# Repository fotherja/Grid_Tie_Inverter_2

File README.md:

# Grid_Tie_Inverter_2
Version 2 of the GTI project

Here are the Eagle files for the grid tie inverter H-Bridge and voltage sense board.

And all the software that runs on and STM32f407 dev board.

Please see a full description of the project on instrucatbles

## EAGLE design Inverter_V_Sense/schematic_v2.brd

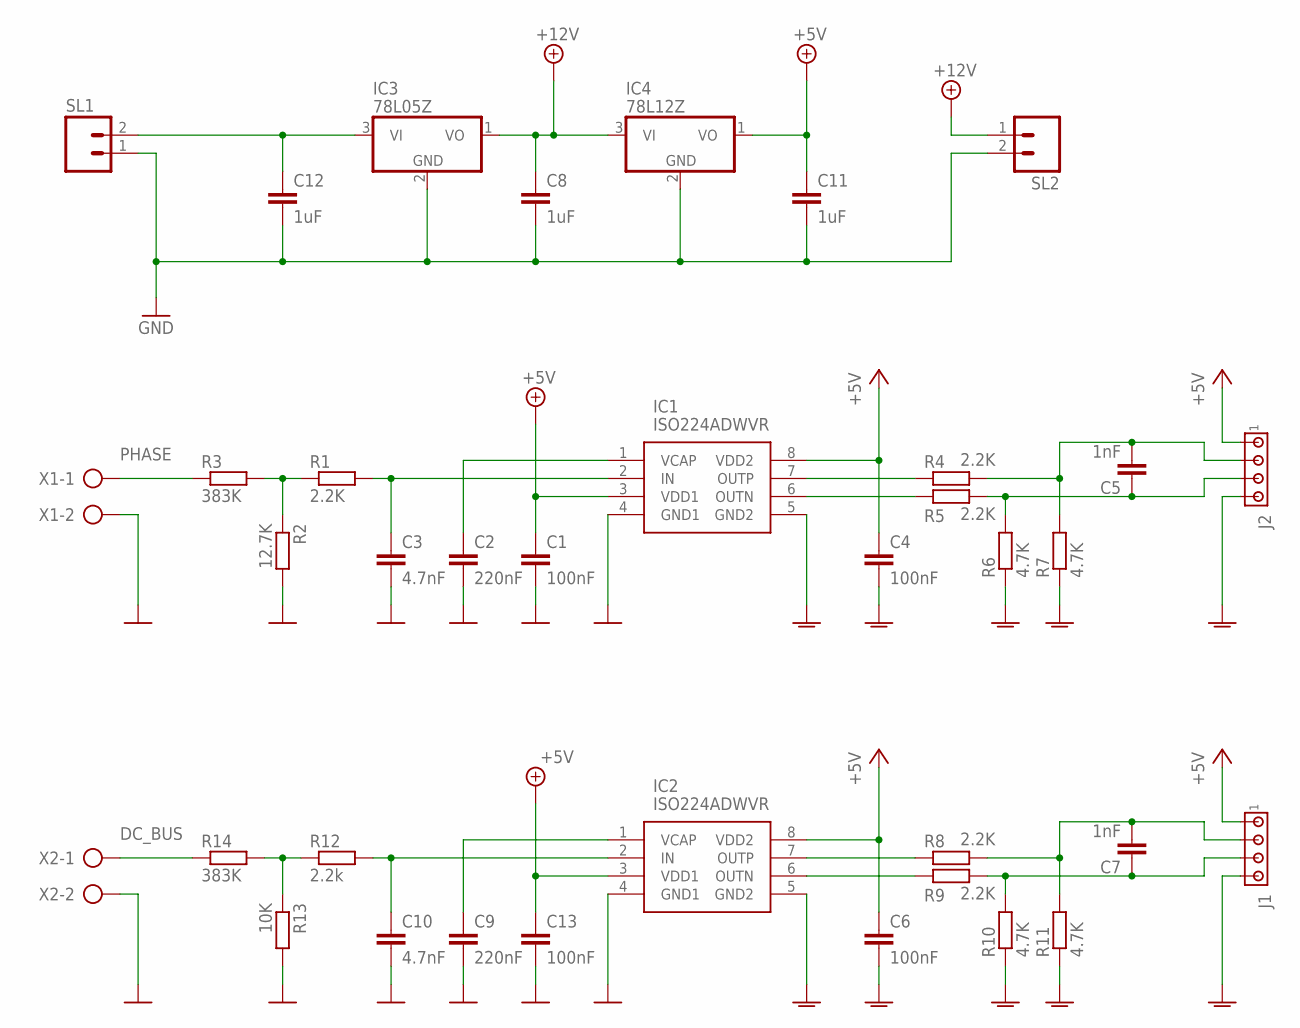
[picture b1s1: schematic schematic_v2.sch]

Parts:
C1, C4, C6, C13: 100nF; C0805
C2, C9: 220nF; C0805
C3, C10: 4.7nF; C0805
C5, C7: 1nF; C0805
C8, C11, C12: 1uF; C0805
IC1, IC2: ISO224ADWVR; SOIC127P1150X280-8N
IC3: 78L05Z; TO92
IC4: 78L12Z; TO92
J1, J2: MTA04-100; 10X04MTA
R1, R4, R5, R8, R9: 2.2K; R0805
R2: 12.7K; 0207/10
R3, R14: 383K; 0207/10
R6, R7, R10, R11: 4.7K; R0805
R12: 2.2k; R0805
R13: 10K; 0207/10
SL1, SL2: M02; 02P
X1, X2: AK500/2

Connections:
+5V: C1.1, C4.1, C6.1, C11.1, C13.1, IC1.3 (VDD1), IC1.8 (VDD2), IC2.3 (VDD1), IC2.8 (VDD2), IC4.1 (VO), J1.1, J2.1
+12V: C8.1, IC3.1 (VO), IC4.3 (VI), SL2.1
DC_BUS: R14.1, X2.1
GND: C1.2, C2.2, C3.2, C8.2, C9.2, C10.2, C11.2, C12.2, C13.2, IC1.4 (GND1), IC2.4 (GND1), IC3.2 (GND), IC4.2 (GND), R2.2, R13.2, SL1.1, SL2.2, X1.2, X2.2
GNDA: C4.2, C6.2, IC1.5 (GND2), IC2.5 (GND2), J1.4, J2.4, R6.1, R7.1, R10.1, R11.1
unnamed: C12.1, IC3.3 (VI), SL1.2
unnamed: C2.1, IC1.1 (VCAP)
unnamed: C3.1, IC1.2 (IN), R1.2
unnamed: R1.1, R2.1, R3.2
unnamed: IC2.7 (OUTP), R8.1
unnamed: IC1.7 (OUTP), R4.1
unnamed: IC1.6 (OUTN), R5.1
unnamed: C5.1, J2.3, R5.2, R6.2
unnamed: C5.2, J2.2, R4.2, R7.2
unnamed: IC2.6 (OUTN), R9.1
unnamed: C7.1, J1.3, R9.2, R10.2
unnamed: C7.2, J1.2, R8.2, R11.2
unnamed: C10.1, IC2.2 (IN), R12.2
unnamed: R12.1, R13.1, R14.2
unnamed: C9.1, IC2.1 (VCAP)
PHASE: R3.1, X1.1

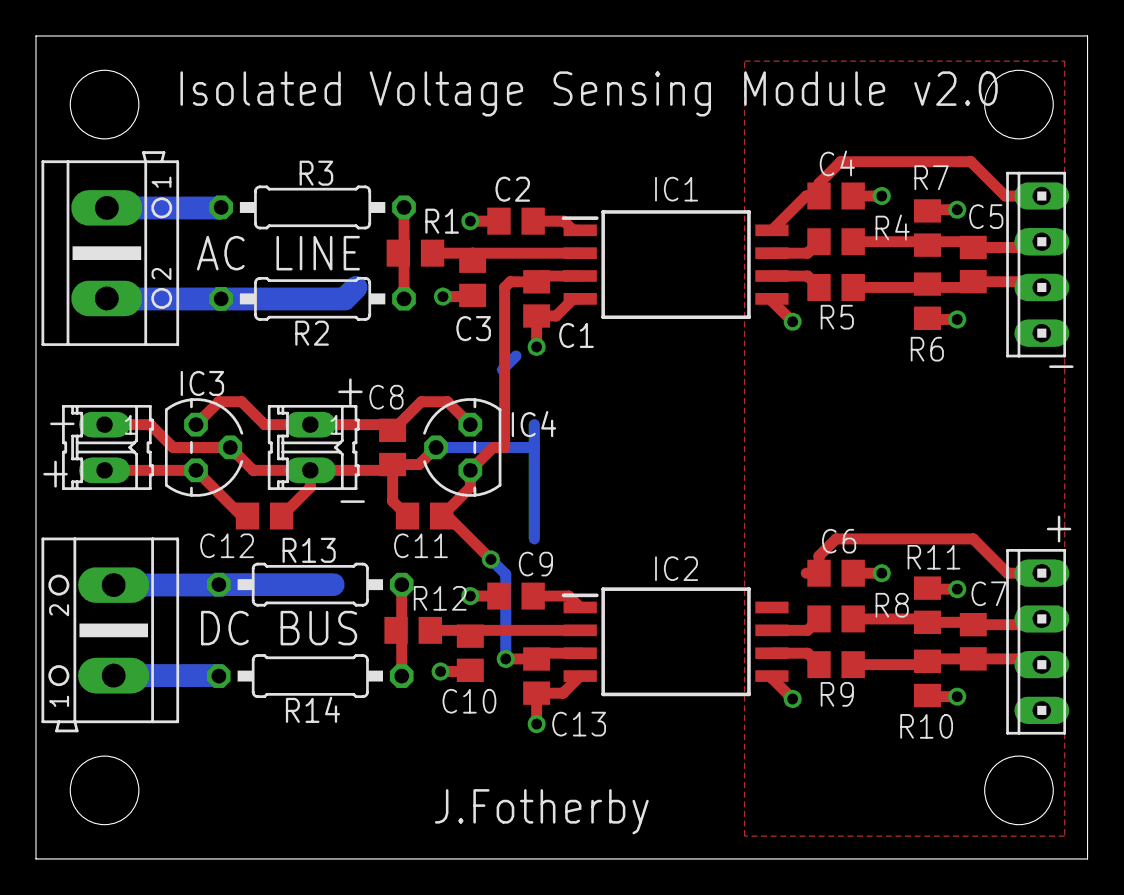
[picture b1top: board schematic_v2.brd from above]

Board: 2 copper layers, 58.4 x 45.7 mm, 37 parts (0 on the bottom side), 21 nets.

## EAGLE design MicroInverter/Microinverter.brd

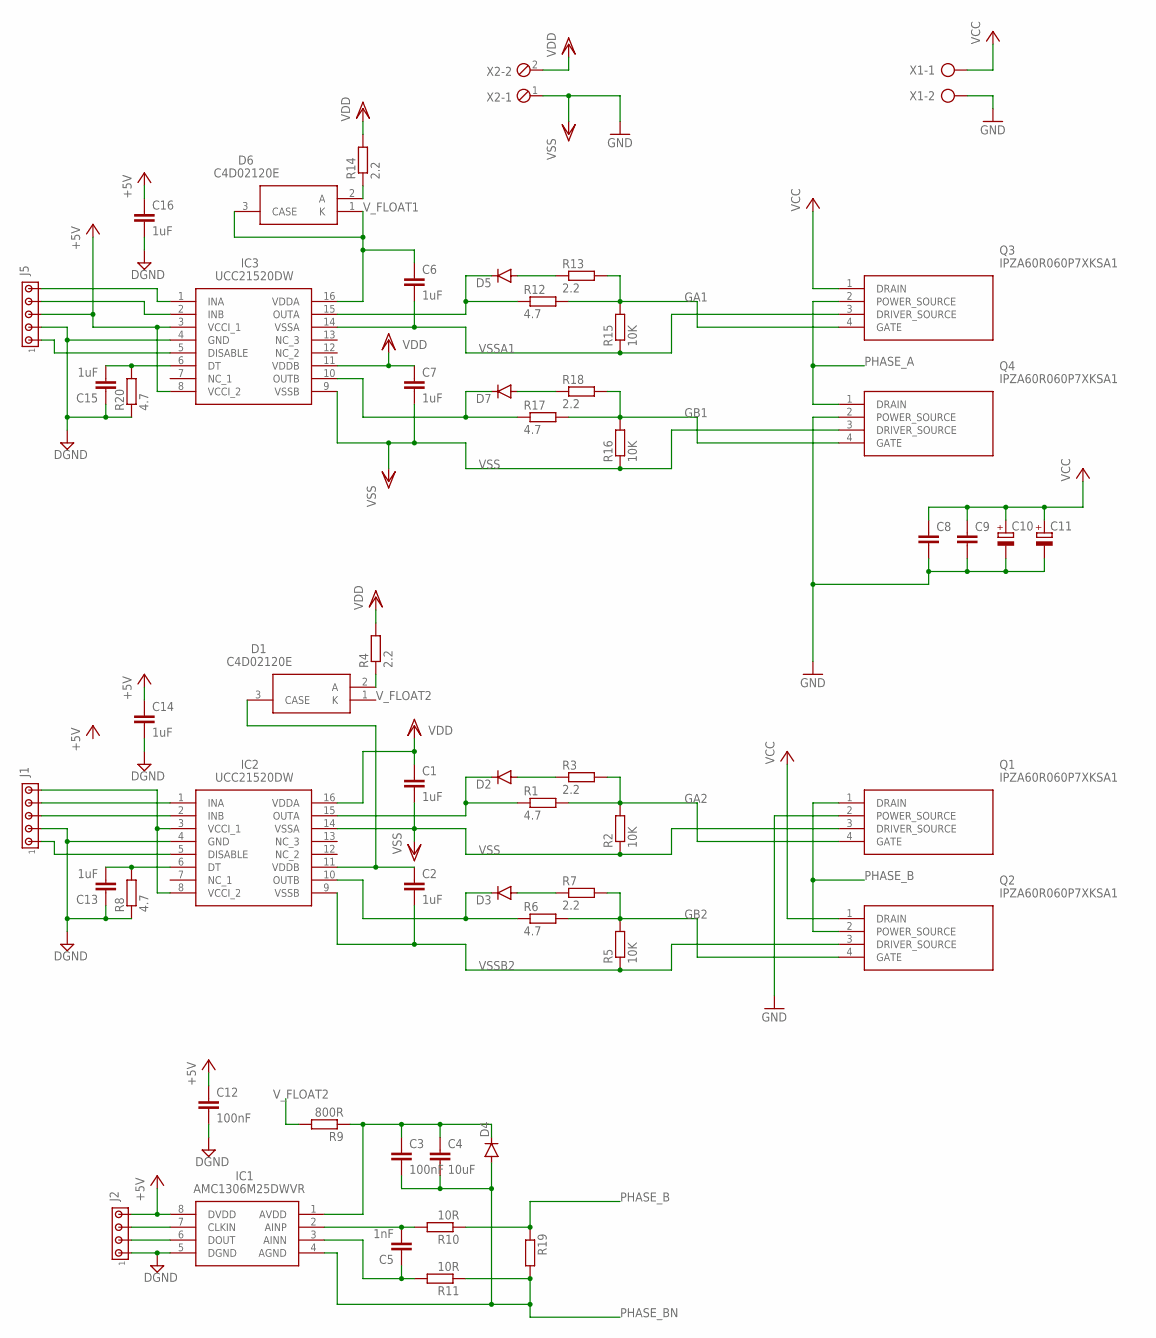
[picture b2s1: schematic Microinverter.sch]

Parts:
C1, C2, C6, C7, C13, C14, C15, C16: 1uF; C0805
C3, C12: 100nF; C0805
C4: 10uF; C0805
C5: 1nF; C0805
C8, C9: C-EUC1210K; C1210K
C10, C11: CPOL-EUSANYO_H; SANYO-OSCON_H
D1, D6: C4D02120E; C3D06065E
D2, D3, D4, D5, D7: MBR0520LT; SOD123
IC1: AMC1306M25DWVR; SOIC127P1150X280-8N
IC2, IC3: UCC21520DW; SOIC127P1030X265-16N
J1, J5: MTA05-100; 10X05MTA
J2: MTA04-100; 10X04MTA
Q1, Q2, Q3, Q4: IPZA60R060P7XKSA1
R1, R6, R8, R12, R17, R20: 4.7; R0805
R2, R5, R15, R16: 10K; R0805
R3, R4, R7, R13, R14, R18: 2.2; R0805
R9: 800R; R0805
R10, R11: 10R; R0805
R19: R-EU_R2512; R2512
X1: AK500/2
X2: MPT2; 2POL254

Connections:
+5V: C12.1, C14.1, C16.1, IC1.8 (DVDD), IC3.3 (VCCI_1), IC3.8 (VCCI_2), J2.4, J5.3
AVDD: C3.1, C4.1, D4.C, IC1.1 (AVDD), R9.1
CLKIN: IC1.7 (CLKIN), J2.3
DGND: C12.2, C13.1, C14.2, C15.1, C16.2, IC1.5 (DGND), IC2.4 (GND), IC3.4 (GND), J1.2, J2.1, J5.2, R8.1, R20.1
DOUT: IC1.6 (DOUT), J2.2
GA1: Q3.4 (GATE), R12.2, R13.2, R15.2
GA2: Q1.4 (GATE), R1.2, R2.2, R3.2
GB1: Q4.4 (GATE), R16.2, R17.2, R18.2
GB2: Q2.4 (GATE), R5.2, R6.2, R7.2
GND: C8.2, C9.2, C10.-, C11.-, Q1.2 (POWER_SOURCE), Q4.2 (POWER_SOURCE), X1.2
unnamed: D2.A, R3.1
unnamed: D3.A, R7.1
unnamed: C5.2, IC1.2 (AINP), R10.2
unnamed: D6.2 (A), R14.1
unnamed: D5.A, R13.1
unnamed: D7.A, R18.1
unnamed: D1.2 (A), R4.1
unnamed: C5.1, IC1.3 (AINN), R11.2
unnamed: IC2.1 (INA), J1.4
unnamed: C13.2, IC2.6 (DT), R8.2
unnamed: IC2.2 (INB), J1.3
unnamed: IC2.5 (DISABLE), J1.1
unnamed: C15.2, IC3.6 (DT), R20.2
unnamed: IC3.2 (INB), J5.4
unnamed: IC3.5 (DISABLE), J5.1
unnamed: IC2.3 (VCCI_1), IC2.8 (VCCI_2), J1.5
unnamed: IC3.1 (INA), J5.5
OUTA: D2.C, IC2.15 (OUTA), R1.1
OUTA1: D5.C, IC3.15 (OUTA), R12.1
OUTB1: D7.C, IC3.10 (OUTB), R17.1
P7: D3.C, IC2.10 (OUTB), R6.1
PHASE_A: Q3.2 (POWER_SOURCE), Q4.1 (DRAIN)
PHASE_B: Q1.1 (DRAIN), Q2.2 (POWER_SOURCE), R10.1, R19.1
PHASE_BN: C3.2, C4.2, D4.A, IC1.4 (AGND), R11.1, R19.2
VCC: C8.1, C9.1, C10.+, C11.+, Q2.1 (DRAIN), Q3.1 (DRAIN), X1.1
VDD: C1.1, C7.1, IC2.16 (VDDA), IC3.11 (VDDB), R4.2, R14.2, X2.2
VSS: C1.2, C7.2, IC2.14 (VSSA), IC3.9 (VSSB), Q1.3 (DRIVER_SOURCE), Q4.3 (DRIVER_SOURCE), R2.1, R16.1, X2.1
VSSA1: C6.2, IC3.14 (VSSA), Q3.3 (DRIVER_SOURCE), R15.1
VSSB2: C2.2, IC2.9 (VSSB), Q2.3 (DRIVER_SOURCE), R5.1
V_FLOAT1: C6.1, D6.1 (K), D6.3 (CASE), IC3.16 (VDDA)
V_FLOAT2: C2.1, D1.3 (CASE), IC2.11 (VDDB), R9.2

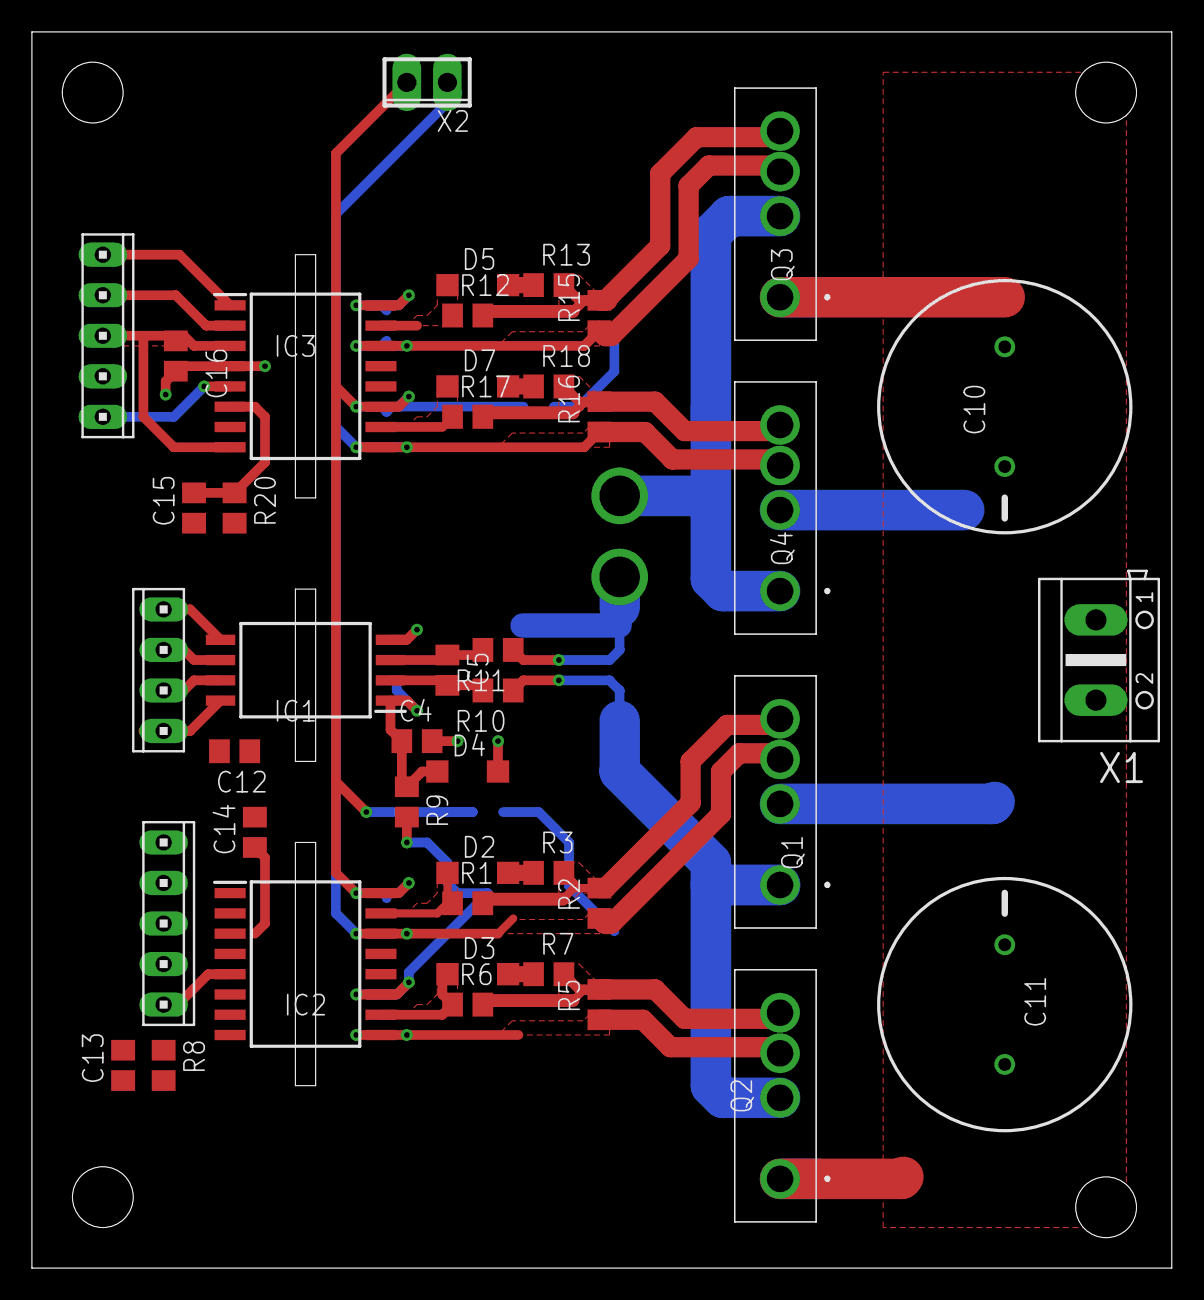
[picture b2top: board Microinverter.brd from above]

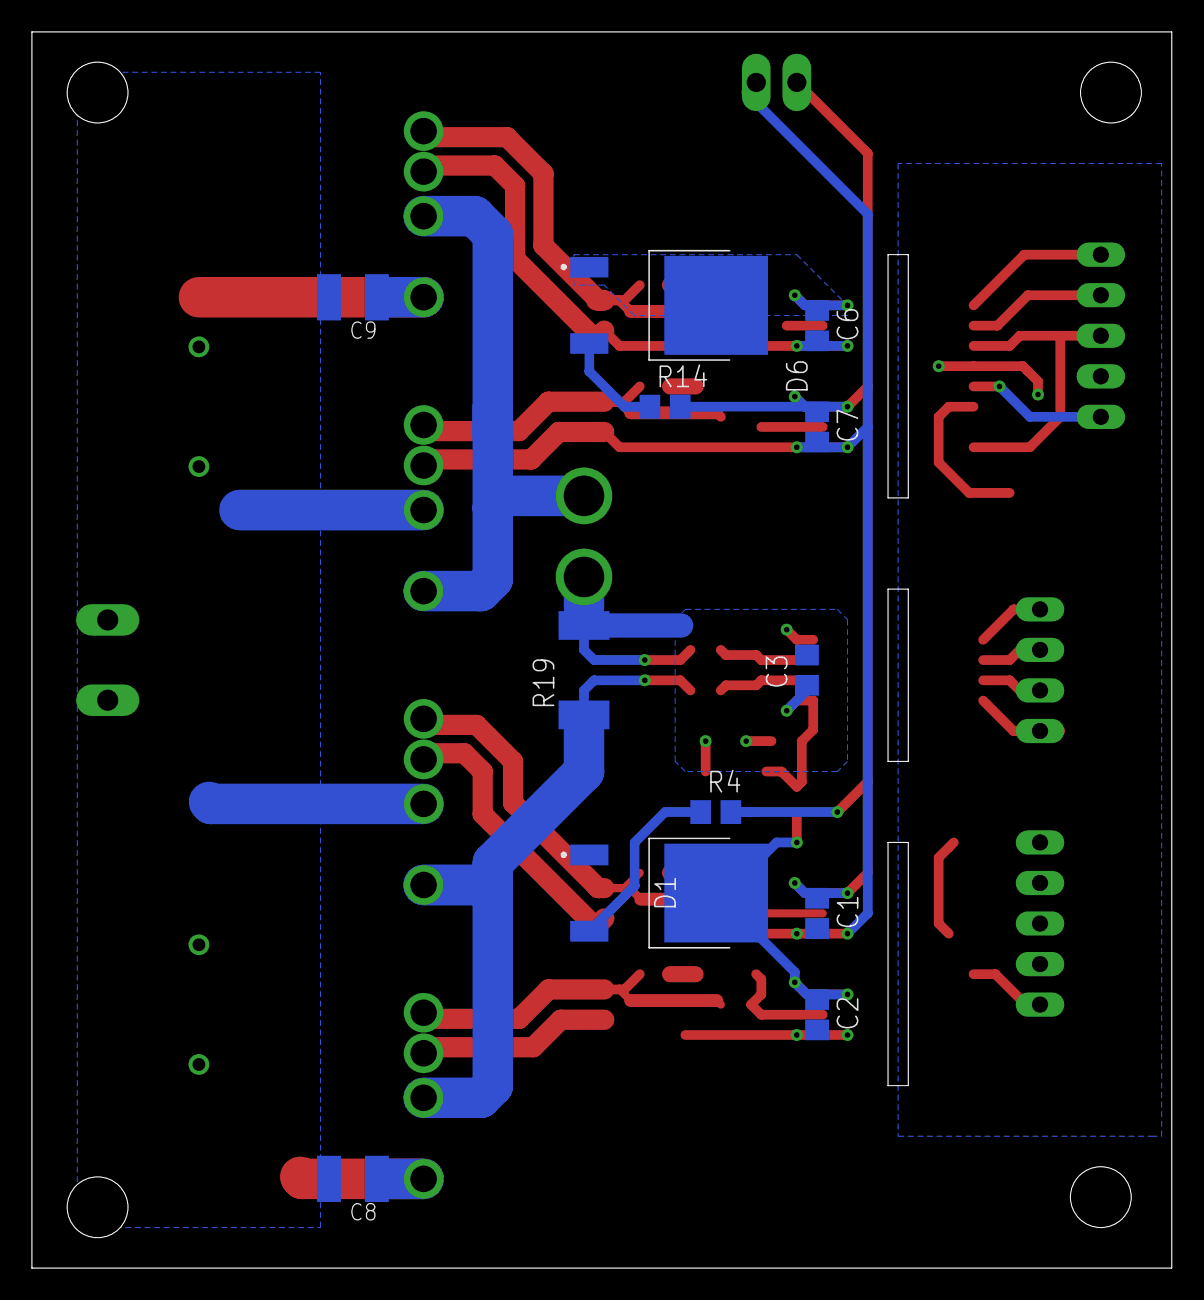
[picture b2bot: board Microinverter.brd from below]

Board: 2 copper layers, 71.4 x 77.5 mm, 55 parts (12 on the bottom side), 41 nets.

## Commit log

2021-06-01 fully working code
2021-06-01 Add eagle files for H-Bridge and Voltage sense brd
